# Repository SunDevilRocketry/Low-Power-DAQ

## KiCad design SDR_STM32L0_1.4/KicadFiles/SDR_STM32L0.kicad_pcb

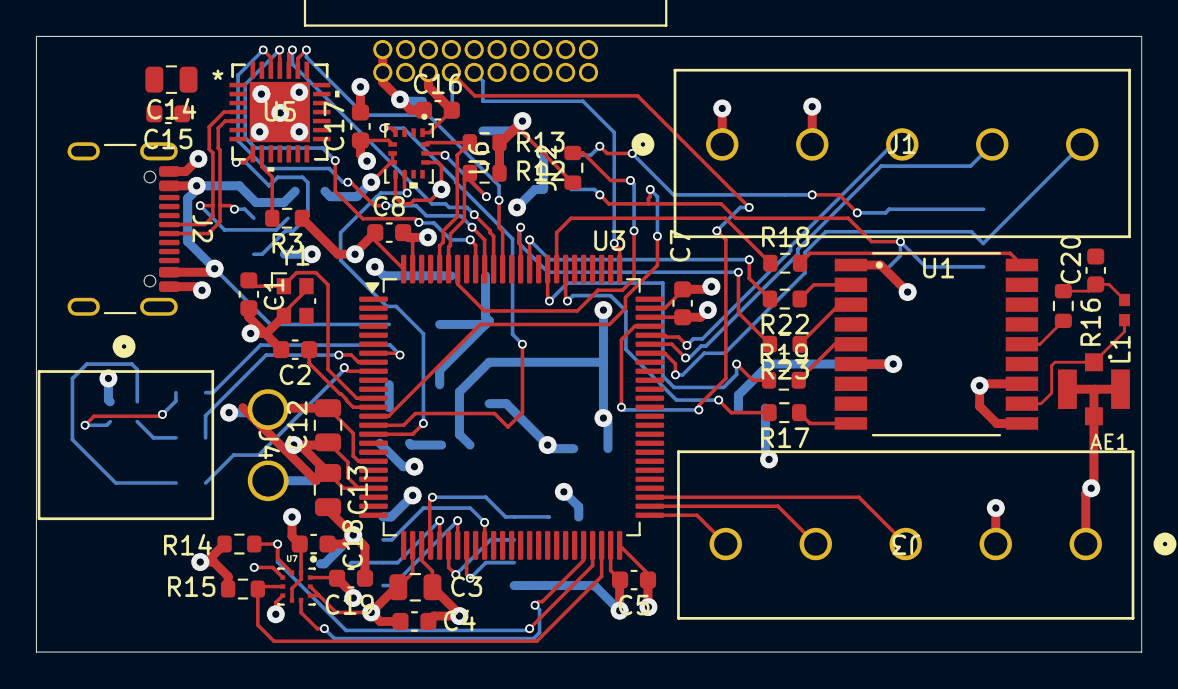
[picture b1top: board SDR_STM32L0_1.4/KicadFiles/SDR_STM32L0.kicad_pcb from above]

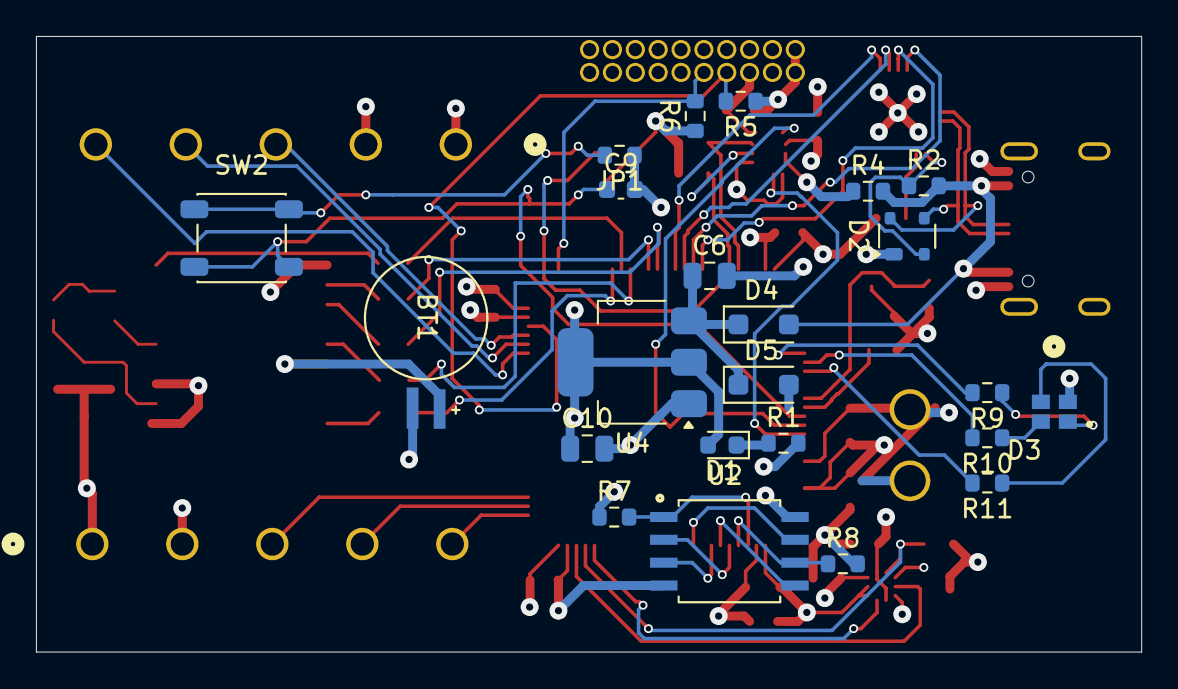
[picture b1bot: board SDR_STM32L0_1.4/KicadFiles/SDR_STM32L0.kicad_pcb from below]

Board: 4 copper layers, 61.4 x 34.2 mm, 68 parts (23 on the bottom side), 60 nets.

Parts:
AE1: 0734120110; 73412-0110
BT1: MS614SE-FL28E; MS621FE-FL11E
C1, C2: 25pF; C_0603_1608Metric
C3, C6: 10u; C_0805_2012Metric
C4, C5, C7, C8: 100n; C_0603_1608Metric
C9, C16, C17, C18, C19: 0.1uF; C_0603_1608Metric
C10: 22u; C_0805_2012Metric
C12: 1u; C_0805_2012Metric
C13: 0.1u; C_0805_2012Metric
C14: 4.7 uF; C_0805_2012Metric
C15: 0.1 uF; C_0603_1608Metric
C20: 0.01uF; C_0603_1608Metric
D1: LED; LED_0603_1608Metric
D2: SP0503BAHT; SOT-143
D3: LED_RGBA; CLMVC-FKA-CL1D1L71BB7C3C3
D4, D5: 5V; D_SOD-123F
H1, H2, H3, H4: MountingHole; MountingHole_2.2mm_M2
J1, J3: Conn_01x05_Pin; CONN_1935190_PXC
J2: USB_C_Receptacle_USB2.0_16P; USB_C_Receptacle_GCT_USB4105-xx-A_16P_TopMnt_Horizontal
J4: Conn_01x02_Pin; CONN2_647676-2_TEC
JP1, JP2: Open Jumper; R_0603_1608Metric
L1: 27nH; L-07C27NJV6T
P1: 3220-20-0200-00
R1: 1.5kR; R_0603_1608Metric
R2: 22.1 kOhm; R_0603_1608Metric
R3: 1kOhm; R_0603_1608Metric
R4: 47.5 kOhm; R_0603_1608Metric
R5, R6, R7, R8: 10k; R_0603_1608Metric
R9: 280; R_0603_1608Metric
R10: 82; R_0603_1608Metric
R11: 68; R_0603_1608Metric
R12, R13: 10kOhm; R_0603_1608Metric
R14, R15: 4.7k; R_0603_1608Metric
R16: 10; R_0603_1608Metric
R17, R18, R19, R22, R23: 33; R_0603_1608Metric
SW2: RESET SWITCH; SW_SPST_PTS647_Sx38
U1: MAX-8C-0-10; MAX-8C-0
U2: Engine-Controller_SST25VF040B-50-4I-S2AE-T; SST25VF040B-50-4I-S2AE-T
U3: STM32L083VBTx; LQFP-100_14x14mm_P0.5mm
U4: AMS1117-3.3; SOT-223-3_TabPin2
U5: CP2102N-Axx-xQFN28; QFN28_5X5_SIL
U6: BMI323
U7: BMP390
Y1: 25 MHz; Crystal_SMD_Abracon_ABM10-4Pin_2.5x2.0mm

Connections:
+3.3V: C3.1, C4.1, C5.1, C7.1, C8.1, C10.1, C12.1, C13.1, C14.1, C15.1, C16.1, C17.1, C18.1, C19.1, D1.2 (A), D3.4 (A), J1.2, J3.2, JP2.1 (A), P1.1, P1.2, R3.1, R5.1, R6.1, R7.1, R12.1, R13.1, R14.1, R15.1, U1.7 (VCC_IO), U1.8 (VCC), U2.8 (VDD), U3.22 (VDDA), U3.28 (VDD), U3.50 (VDD), U3.73 (VDD), U3.100 (VDD), U4.2 (VO), U5.6 (VDD), U5.7 (VREGIN), U6.5 (VDDIO), U6.8 (VDD), U6.12 (CSB), U7.1 (VDDIO), U7.6 (CSB), U7.10 (VDD)
/Movement/3V_BAK: BT1.1 (+), U1.6 (V_BCKP)
/Movement/GPS: AE1.1 (A), L1.2, U1.11 (RF_IN)
BOOT0: JP2.2 (B), U3.94 (BOOT0)
BOUTPUT: R11.2, U3.9 (PC15)
EXTI_10: U3.15 (PC0), U6.4 (INT1)
EXTI_11: U3.16 (PC1), U6.9 (INT2)
EXTI_13: R19.1, U3.84 (PD3)
EXTI_15: U3.46 (PE15), U7.7 (INT)
GND: AE1.2 (Shield), BT1.2 (-), C1.2, C2.2, C3.2, C4.2, C5.2, C6.2, C7.2, C8.2, C9.2, C10.2, C12.2, C13.2, C14.2, C15.2, C16.2, C17.2, C18.2, C19.2, C20.2, D2.1 (A), J1.1, J2.A1 (GND), J2.A12 (GND), J2.B1 (GND), J2.B12 (GND), J3.1, J4.1, JP1.1 (A), P1.3, P1.4, P1.5, P1.6, P1.8, P1.10, P1.12, P1.14, P1.16, P1.18, P1.20, R1.2, R4.1, R8.2, U1.1 (GND), U1.10 (GND), U1.12 (GND), U2.4 (VSS), U3.19 (VSSA), U3.27 (VSS), U3.49 (VSS), U3.74 (VSS), U3.99 (VSS), U4.1 (GND), U5.3 (GND), U5.29 (GND), U6.1 (SDO), U6.6 (GNDIO), U6.7 (GND), U7.3 (VSS), U7.5 (SDO), U7.8 (VSS), U7.9 (VSS), Y1.2, Y1.4
GOUTPUT: R10.2, U3.8 (PC14)
GPIO3_ADC: J3.5, U3.51 (PB12)
GPIO3_INPUT: J3.3, U3.53 (PB14)
GPIO3_OUTPUT: J3.4, U3.52 (PB13)
GPIO4_ADC: J1.5, U3.69 (PA10)
GPIO4_INPUT: J1.3, U3.71 (PA12)
GPIO4_OUTPUT: J1.4, U3.70 (PA11)
GPIO_GPSRST: R17.2, U3.82 (PD1)
GPIO_GPSSB: R18.1, U3.83 (PD2)
GPIO_OUTFL: U2.3 (*WP), U3.33 (PC4)
I2C1_SCL: R12.2, U3.95 (PB8), U6.13 (SCX)
I2C1_SDA: R13.2, U3.96 (PB9), U6.14 (SDX)
I2C2_SCL: R14.2, U3.47 (PB10), U7.2 (SCK)
I2C2_SDA: R15.2, U3.48 (PB11), U7.4 (SDI)
NRST: C9.1, P1.15, SW2.2 (B), U3.14 (NRST)
unnamed: C20.1, L1.1, R16.1
unnamed: D1.1 (K), R1.1
unnamed: D3.3 (BK), R11.1
unnamed: D3.2 (GK), R10.1
unnamed: D3.1 (RK), R9.1
unnamed: C6.1, D4.1 (K), D5.1 (K), U4.3 (VI)
unnamed: D5.2 (A), J4.2
unnamed: JP1.2 (B), SW2.1 (A)
unnamed: R19.2, U1.5 (EXTINT)
unnamed: R23.1, U1.3 (RXD)
unnamed: R22.1, U1.2 (TXD)
unnamed: R16.2, U1.14 (VCC_RF)
unnamed: R17.1, U1.9 (~RESET)
unnamed: R18.2, U1.18 (~SAFEBOOT)
unnamed: D2.4 (K), J2.A6 (D+), U5.4 (D+)
unnamed: D2.3 (K), J2.A7 (D-), U5.5 (D-)
unnamed: D2.2 (K), R2.1, U5.8 (VBUS)
unnamed: R3.2, U5.9 (~RST)
OSC_IN: C1.1, U3.12 (PH0), Y1.1
OSC_OUT: C2.1, U3.13 (PH1), Y1.3
ROUTPUT: R9.2, U3.7 (PC13)
SPI1_MISO: U2.2 (SO), U3.31 (PA6)
SPI1_MOSI: U2.5 (SI), U3.32 (PA7)
SPI1_NSS: R7.2, U2.1 (*CE), U3.29 (PA4)
SPI1_SCK: R8.1, U2.6 (SCK), U3.30 (PA5)
SYS_SWCLK: P1.9, R6.2, U3.76 (PA14)
SYS_SWDIO: P1.7, R5.2, U3.72 (PA13)
TIM3_CH3: U2.7 (*HOLD), U3.35 (PB0)
USART1_CTS: U3.90 (PB4), U5.24 (~RTS)
USART1_RTS: U3.89 (PB3), U5.23 (~CTS)
USART1_RX: U3.92 (PB6), U5.25 (RXD)
USART1_TX: U3.91 (PB5), U5.26 (TXD)
USART2_RX: R23.2, U3.87 (PD6)
USART2_TX: R22.2, U3.86 (PD5)
VBUS: D4.2 (A), J2.A4 (VBUS), J2.A9 (VBUS), J2.B4 (VBUS), J2.B9 (VBUS), R2.2, R4.2

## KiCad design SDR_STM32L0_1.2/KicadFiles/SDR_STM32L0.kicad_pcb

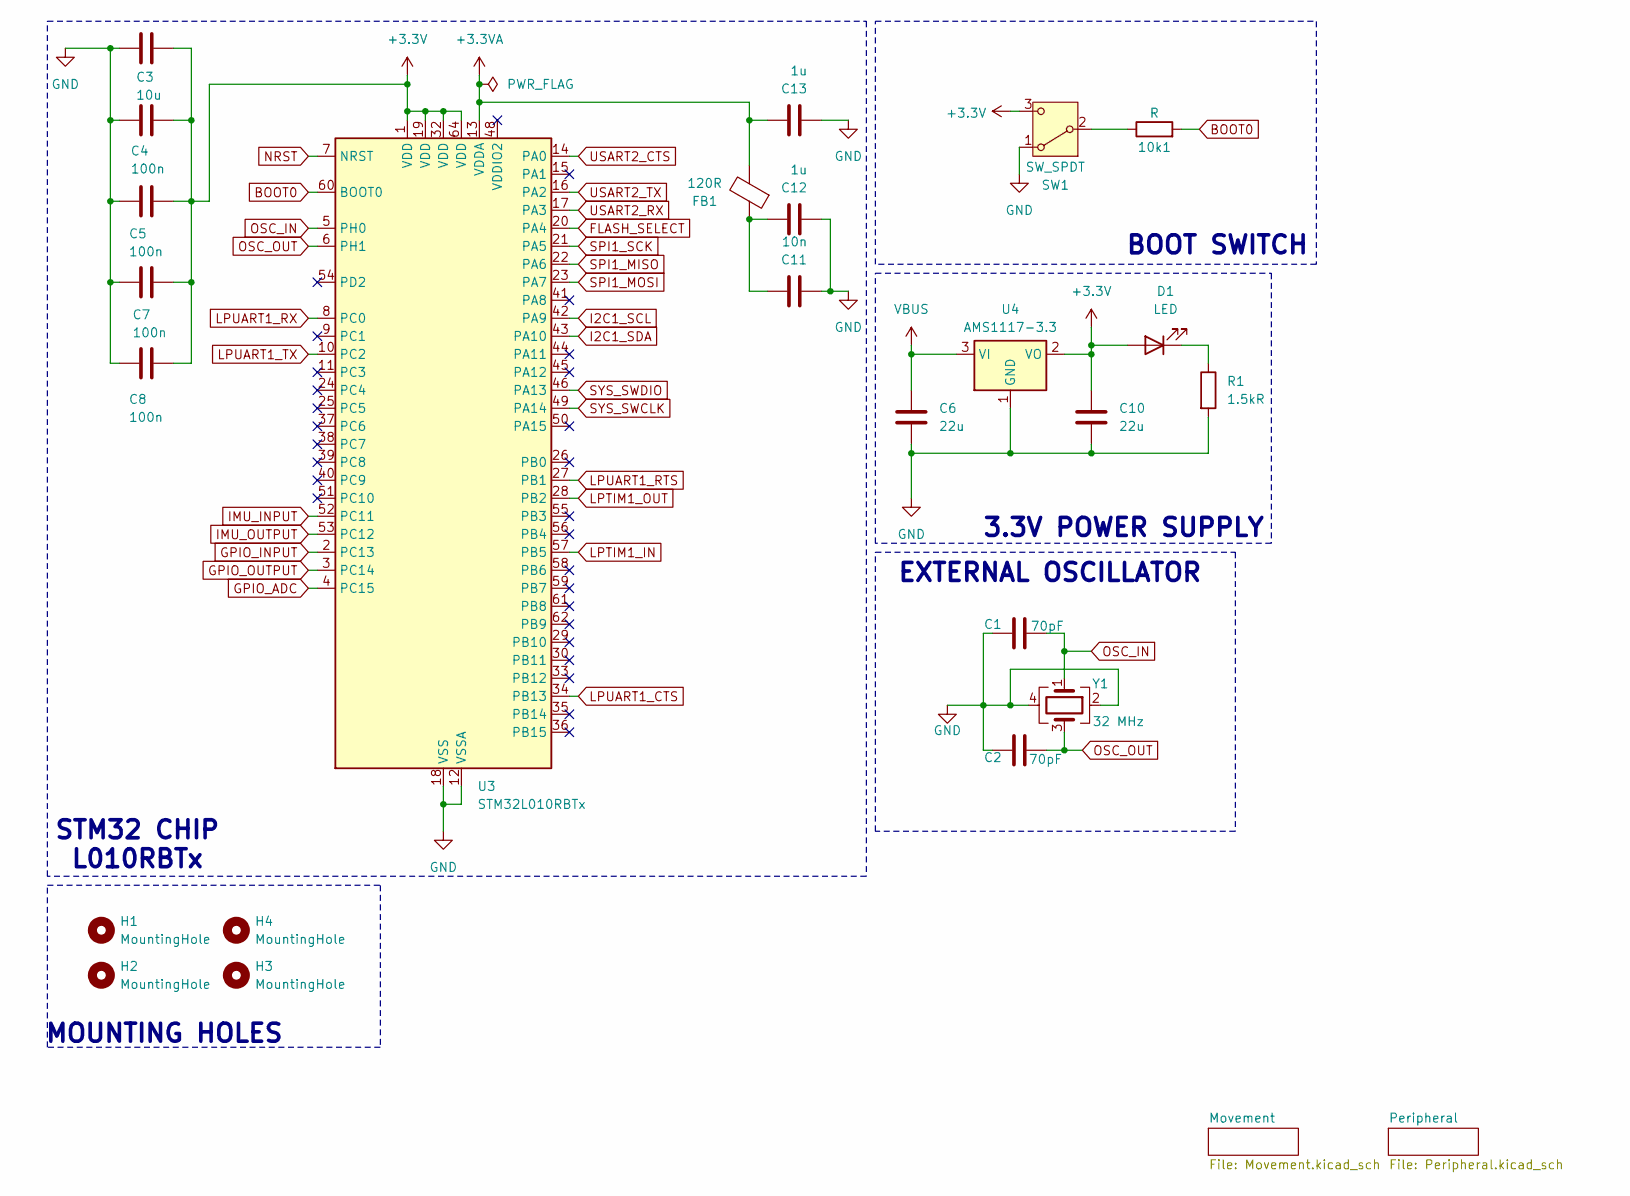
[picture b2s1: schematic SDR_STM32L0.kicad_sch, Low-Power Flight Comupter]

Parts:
10k1: R; R_0402_1005Metric
C1, C2: 70pF; C_0402_1005Metric
C3: 10u; C_0805_2012Metric
C4, C5, C7, C8: 100n; C_0402_1005Metric
C6, C10: 22u; C_0805_2012Metric
C11: 10n; C_0402_1005Metric
C12, C13: 1u; C_0805_2012Metric
D1: LED; LED_0603_1608Metric
FB1: 120R; L_0603_1608Metric
H1, H2, H3, H4: MountingHole; MountingHole_2.2mm_M2
R1: 1.5kR; R_0402_1005Metric
SW1: SW_SPDT; SW_SPST_B3U-1100P-B
U3: STM32L010RBTx; LQFP-64_10x10mm_P0.5mm
U4: AMS1117-3.3; SOT-223-3_TabPin2
Y1: 32 MHz; Crystal_SMD_Abracon_ABM10-4Pin_2.5x2.0mm

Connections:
+3.3V: C3.1, C4.1, C5.1, C7.1, C8.1, C10.1, D1.2 (A), SW1.3 (C), U3.1 (VDD), U3.19 (VDD), U3.32 (VDD), U3.64 (VDD), U4.2 (VO); also elsewhere on the board
+3.3VA: C13.1, FB1.2, U3.13 (VDDA)
BOOT0: 10k1.2, U3.60 (BOOT0)
FLASH_SELECT: U3.20 (PA4); also elsewhere on the board
GND: C1.2, C2.2, C3.2, C4.2, C5.2, C6.2, C7.2, C8.2, C10.2, C11.2, C12.2, C13.2, R1.2, SW1.1 (A), U3.12 (VSSA), U3.18 (VSS), U3.31 (VSS), U3.47 (VSS), U3.63 (VSS), U4.1 (GND), Y1.2, Y1.4; also elsewhere on the board
GPIO_ADC: U3.4 (PC15); also elsewhere on the board
GPIO_INPUT: U3.2 (PC13); also elsewhere on the board
GPIO_OUTPUT: U3.3 (PC14); also elsewhere on the board
I2C1_SCL: U3.42 (PA9); also elsewhere on the board
I2C1_SDA: U3.43 (PA10); also elsewhere on the board
IMU_INPUT: U3.52 (PC11); also elsewhere on the board
IMU_OUTPUT: U3.53 (PC12); also elsewhere on the board
LPTIM1_IN: U3.57 (PB5); also elsewhere on the board
LPTIM1_OUT: U3.28 (PB2); also elsewhere on the board
LPUART1_CTS: U3.34 (PB13); also elsewhere on the board
LPUART1_RTS: U3.27 (PB1); also elsewhere on the board
LPUART1_RX: U3.8 (PC0); also elsewhere on the board
LPUART1_TX: U3.10 (PC2); also elsewhere on the board
NRST: U3.7 (NRST); also elsewhere on the board
unnamed: C11.1, C12.1, FB1.1
unnamed: D1.1 (K), R1.1
unnamed: 10k1.1, SW1.2 (B)
OSC_IN: C1.1, U3.5 (PH0), Y1.1
OSC_OUT: C2.1, U3.6 (PH1), Y1.3
SPI1_MISO: U3.22 (PA6); also elsewhere on the board
SPI1_MOSI: U3.23 (PA7); also elsewhere on the board
SPI1_SCK: U3.21 (PA5); also elsewhere on the board
SYS_SWCLK: U3.49 (PA14); also elsewhere on the board
SYS_SWDIO: U3.46 (PA13); also elsewhere on the board
USART2_CTS: U3.14 (PA0); also elsewhere on the board
USART2_RX: U3.17 (PA3); also elsewhere on the board
USART2_TX: U3.16 (PA2); also elsewhere on the board
VBUS: C6.1, U4.3 (VI); also elsewhere on the board

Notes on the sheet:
MOUNTING HOLES
STM32 CHIP L010RBTx
EXTERNAL OSCILLATOR
3.3V POWER SUPPLY
BOOT SWITCH

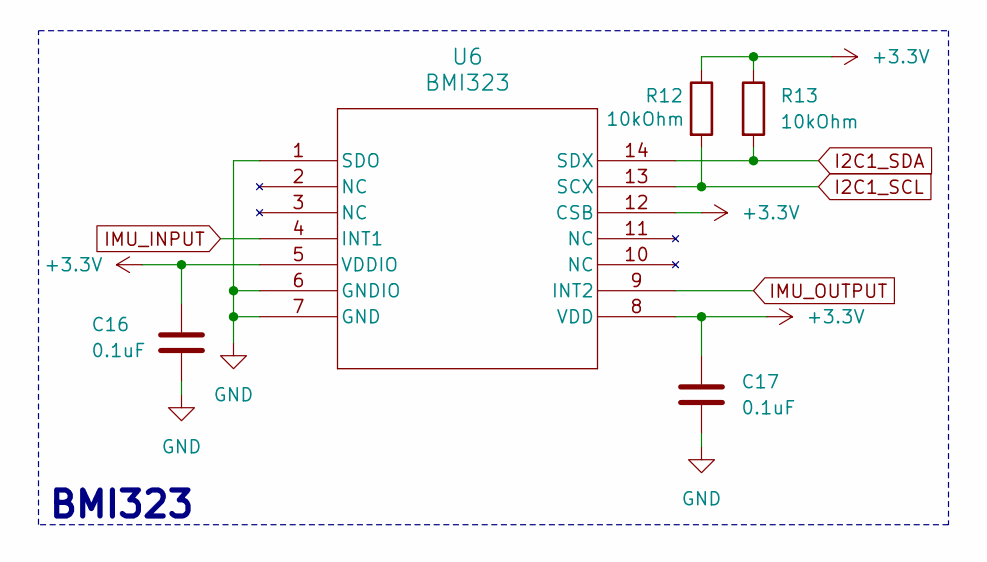
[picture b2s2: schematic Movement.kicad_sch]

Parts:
C16, C17: 0.1uF; C_0402_1005Metric
R12, R13: 10kOhm; R_0402_1005Metric
U6: BMI323

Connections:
+3.3V: C16.1, C17.1, R12.1, R13.1, U6.5 (VDDIO), U6.8 (VDD), U6.12 (CSB); also elsewhere on the board
GND: C16.2, C17.2, U6.1 (SDO), U6.6 (GNDIO), U6.7 (GND); also elsewhere on the board
I2C1_SCL: R12.2, U6.13 (SCX); also elsewhere on the board
I2C1_SDA: R13.2, U6.14 (SDX); also elsewhere on the board
IMU_INPUT: U6.4 (INT1); also elsewhere on the board
IMU_OUTPUT: U6.9 (INT2); also elsewhere on the board

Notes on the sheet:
BMI323

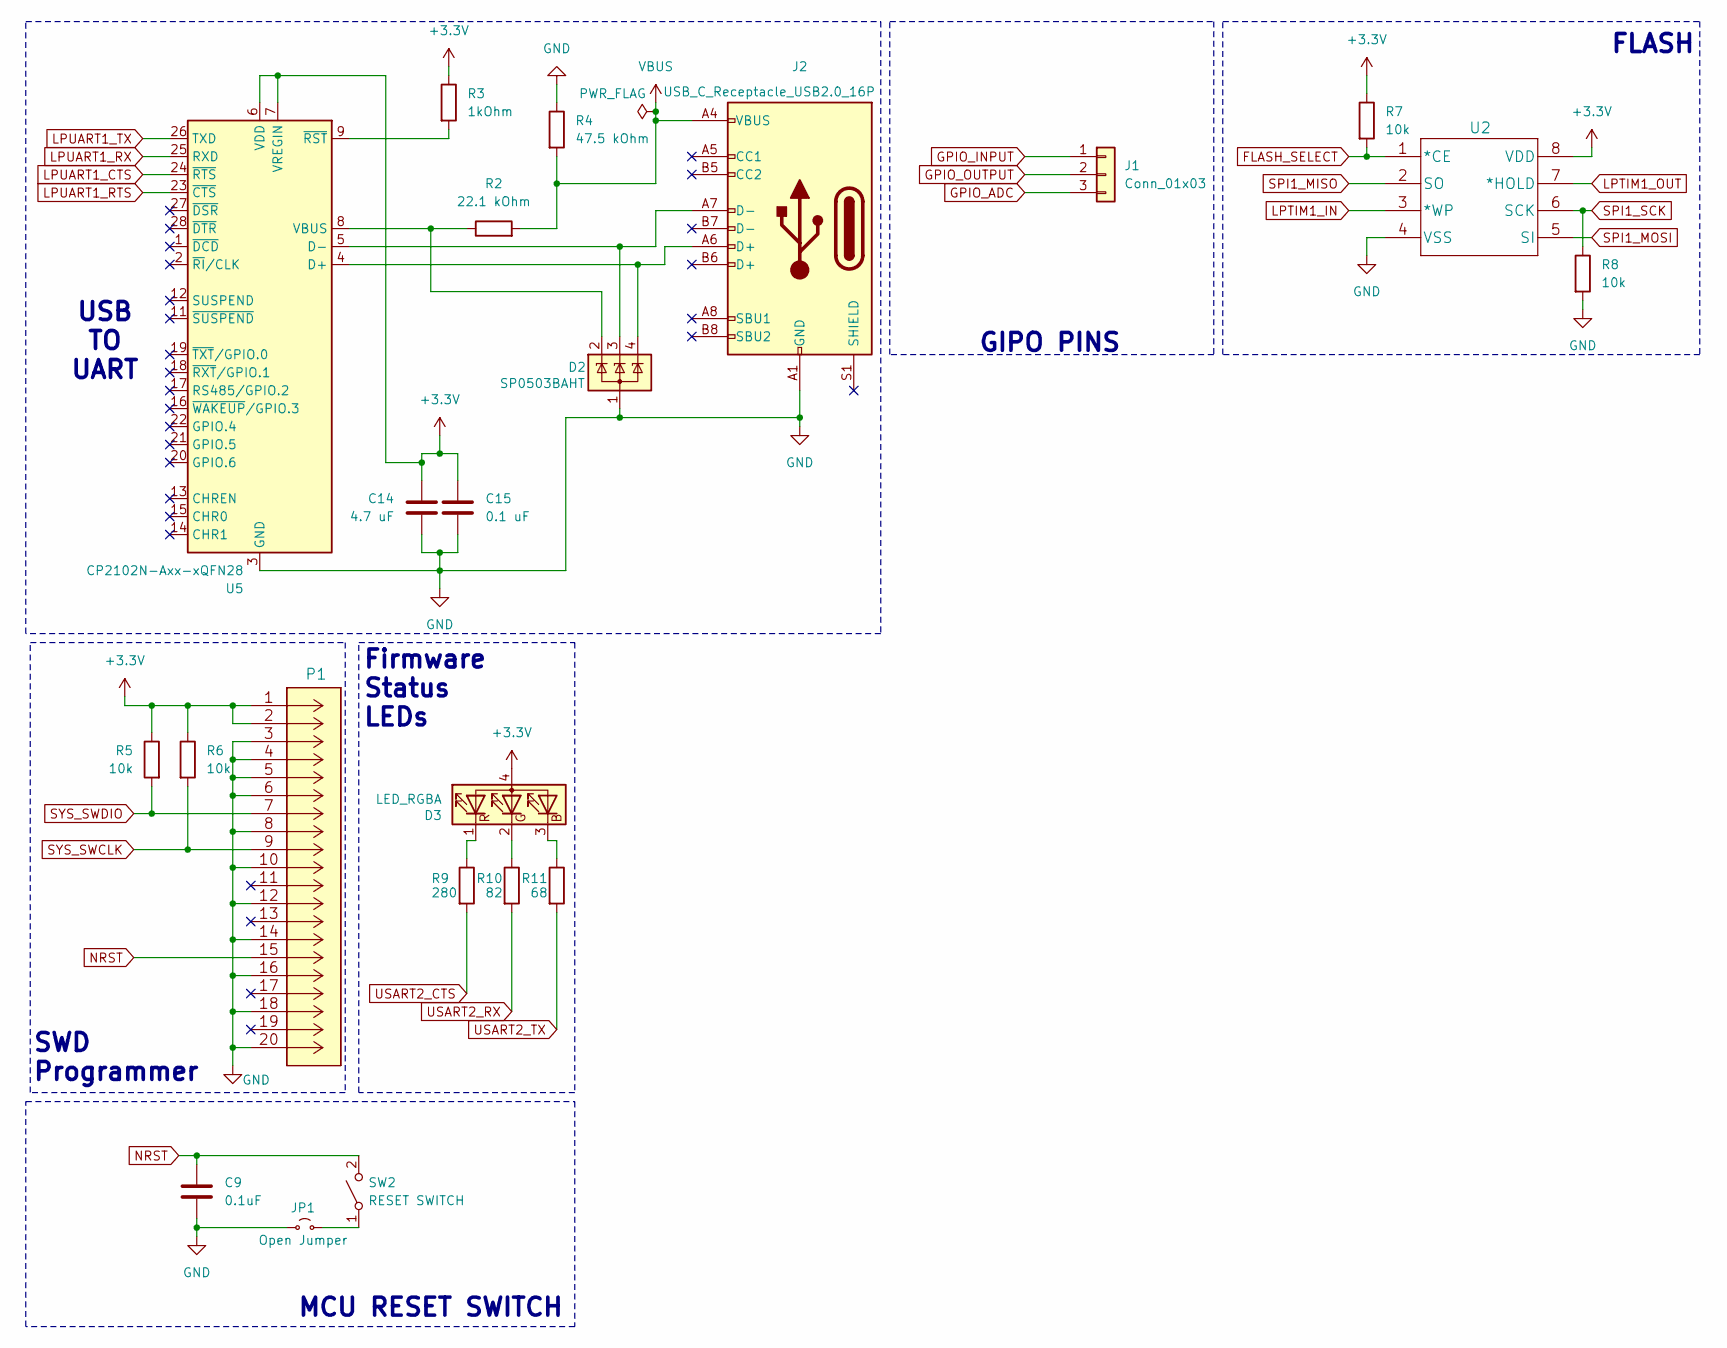
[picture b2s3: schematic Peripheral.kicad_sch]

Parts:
C9: 0.1uF; C_0402_1005Metric
C14: 4.7 uF; C_0805_2012Metric
C15: 0.1 uF; C_0402_1005Metric
D2: SP0503BAHT; SOT-143
D3: LED_RGBA; LED_Cree-PLCC4_5x5mm_CW
J1: Conn_01x03; JST_EH_S3B-EH_1x03_P2.50mm_Horizontal
J2: USB_C_Receptacle_USB2.0_16P; USB_C_Receptacle_GCT_USB4105-xx-A_16P_TopMnt_Horizontal
JP1: Open Jumper; TestPoint_2Pads_Pitch2.54mm_Drill0.8mm
P1: 3220-20-0200-00
R2: 22.1 kOhm; R_0603_1608Metric
R3: 1kOhm; R_0402_1005Metric
R4: 47.5 kOhm; R_0603_1608Metric
R5, R6, R7, R8: 10k; R_0402_1005Metric
R9: 280; R_0402_1005Metric
R10: 82; R_0402_1005Metric
R11: 68; R_0402_1005Metric
SW2: RESET SWITCH; SW_DIP_SPSTx01_Slide_9.78x4.72mm_W7.62mm_P2.54mm
U2: Engine-Controller_SST25VF040B-50-4I-S2AE-T; SST25VF040B-50-4I-S2AE-T
U5: CP2102N-Axx-xQFN28; QFN-28-1EP_5x5mm_P0.5mm_EP3.35x3.35mm

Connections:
+3.3V: C14.1, C15.1, D3.4 (A), P1.1, P1.2, R3.1, R5.1, R6.1, R7.1, U2.8 (VDD), U5.6 (VDD), U5.7 (VREGIN); also elsewhere on the board
FLASH_SELECT: R7.2, U2.1 (*CE); also elsewhere on the board
GND: C9.2, C14.2, C15.2, D2.1 (A), J2.A1 (GND), J2.A12 (GND), J2.B1 (GND), J2.B12 (GND), JP1.1 (A), P1.3, P1.4, P1.5, P1.6, P1.8, P1.10, P1.12, P1.14, P1.16, P1.18, P1.20, R4.1, R8.2, U2.4 (VSS), U5.3 (GND), U5.29 (GND); also elsewhere on the board
GPIO_ADC: J1.3; also elsewhere on the board
GPIO_INPUT: J1.1; also elsewhere on the board
GPIO_OUTPUT: J1.2; also elsewhere on the board
LPTIM1_IN: U2.3 (*WP); also elsewhere on the board
LPTIM1_OUT: U2.7 (*HOLD); also elsewhere on the board
LPUART1_CTS: U5.24 (~RTS); also elsewhere on the board
LPUART1_RTS: U5.23 (~CTS); also elsewhere on the board
LPUART1_RX: U5.25 (RXD); also elsewhere on the board
LPUART1_TX: U5.26 (TXD); also elsewhere on the board
NRST: C9.1, P1.15, SW2.2 (B); also elsewhere on the board
unnamed: D3.3 (BK), R11.1
unnamed: D3.2 (GK), R10.1
unnamed: D3.1 (RK), R9.1
unnamed: JP1.2 (B), SW2.1 (A)
unnamed: D2.4 (K), J2.A6 (D+), U5.4 (D+)
unnamed: D2.3 (K), J2.A7 (D-), U5.5 (D-)
unnamed: D2.2 (K), R2.1, U5.8 (VBUS)
unnamed: R3.2, U5.9 (~RST)
SPI1_MISO: U2.2 (SO); also elsewhere on the board
SPI1_MOSI: U2.5 (SI); also elsewhere on the board
SPI1_SCK: R8.1, U2.6 (SCK); also elsewhere on the board
SYS_SWCLK: P1.9, R6.2; also elsewhere on the board
SYS_SWDIO: P1.7, R5.2; also elsewhere on the board
USART2_CTS: R9.2; also elsewhere on the board
USART2_RX: R10.2; also elsewhere on the board
USART2_TX: R11.2; also elsewhere on the board
VBUS: J2.A4 (VBUS), J2.A9 (VBUS), J2.B4 (VBUS), J2.B9 (VBUS), R2.2, R4.2; also elsewhere on the board

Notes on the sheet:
SWD Programmer
Firmware Status LEDs
FLASH
MCU RESET SWITCH
USB TO UART
GIPO PINS

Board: 2 copper layers, 51 parts (0 on the bottom side), 41 nets, no tracks yet.

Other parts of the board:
SERIAL WIRE DEBUG: 3220-20-0200-00

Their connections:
+3.3V: SERIAL WIRE DEBUG.1, SERIAL WIRE DEBUG.2; also elsewhere on the board
GND: SERIAL WIRE DEBUG.3, SERIAL WIRE DEBUG.4, SERIAL WIRE DEBUG.5, SERIAL WIRE DEBUG.6, SERIAL WIRE DEBUG.8, SERIAL WIRE DEBUG.10, SERIAL WIRE DEBUG.12, SERIAL WIRE DEBUG.14, SERIAL WIRE DEBUG.16, SERIAL WIRE DEBUG.18, SERIAL WIRE DEBUG.20; also elsewhere on the board
NRST: SERIAL WIRE DEBUG.15; also elsewhere on the board
SYS_SWCLK: SERIAL WIRE DEBUG.9; also elsewhere on the board
SYS_SWDIO: SERIAL WIRE DEBUG.7; also elsewhere on the board

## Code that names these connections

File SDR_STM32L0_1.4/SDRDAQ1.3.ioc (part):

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Mcu.Name=STM32L083V(B-Z)Tx
Mcu.Package=LQFP100
Mcu.UserName=STM32L083VBTx
PA0.Mode=CTS_Only
PA0.Signal=USART2_CTS
PA10.Mode=Asynchronous
PA10.Signal=USART1_RX
PA12.Signal=GPIO_Output
PA13.Mode=Serial_Wire
PA13.Signal=SYS_SWDIO
PA14.Mode=Serial_Wire
PA14.Signal=SYS_SWCLK
PA2.Mode=Asynchronous
PA2.Signal=USART2_TX
PA3.Mode=Asynchronous
PA3.Signal=USART2_RX
PA5.Mode=Full_Duplex_Master
PA5.Signal=SPI1_SCK
PA6.Mode=CTS_RTS
PA6.Signal=LPUART1_CTS
PA7.Mode=Full_Duplex_Master
PA7.Signal=SPI1_MOSI
PA9.Mode=Asynchronous
PA9.Signal=USART1_TX
PB1.Mode=CTS_RTS
PB1.Signal=LPUART1_RTS
PB10.Mode=I2C
PB10.Signal=I2C2_SCL
PB11.Mode=I2C
PB11.Signal=I2C2_SDA
PB13.Signal=GPIO_Input
PB14.Signal=GPIO_Output
PB15.Signal=GPIO_Analog
PB2.Mode=WaveformGeneration
PB2.Signal=LPTIM1_OUT
PB6.Mode=I2C
PB6.Signal=I2C1_SCL
PB7.Mode=I2C
PB7.Signal=I2C1_SDA
PC0.Mode=Counts_external_clock_standalone_1X_occur1
PC0.Signal=LPTIM1_IN1
PC1.Mode=Asynchronous
PC1.Signal=LPUART1_TX
PC13.Signal=GPIO_Output
PC14-OSC32_IN.Signal=GPIO_Input
PC15-OSC32_OUT.Signal=GPIO_Analog
PC2.Signal=GPIO_Analog
PC3.Signal=GPIO_Output
PC5.Mode=Asynchronous
PC5.Signal=LPUART1_RX
PD0.Signal=GPIO_Input
PD1.Signal=GPIO_Output
PD10.Signal=GPIO_Output
PD11.Signal=GPIO_Output
PD12.Signal=GPIO_Output
PD2.Signal=GPIO_Analog
PD8.Signal=GPIO_Output
PD9.Signal=GPIO_Input
PE10.Signal=GPIO_Output
PE14.Mode=Full_Duplex_Master
PE14.Signal=SPI1_MISO
PE15.Signal=GPIO_Output
PH0-OSC_IN.Mode=HSE-External-Oscillator
PH0-OSC_IN.Signal=RCC_OSC_IN
PH1-OSC_OUT.Mode=HSE-External-Oscillator
PH1-OSC_OUT.Signal=RCC_OSC_OUT
PH10.Signal=GPIO_Input
RCC.HSE_VALUE=8000000
RCC.SYSCLKFreq_VALUE=2097000
board=custom

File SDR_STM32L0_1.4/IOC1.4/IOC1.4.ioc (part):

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Mcu.Name=STM32L083V(B-Z)Tx
Mcu.Package=LQFP100
Mcu.UserName=STM32L083VBTx
PA0.Signal=GPIO_Analog
PA1.Signal=GPIO_Output
PA10.Signal=GPIO_Analog
PA11.Signal=GPIO_Output
PA12.Signal=GPIO_Input
PA13.Mode=Serial_Wire
PA13.Signal=SYS_SWDIO
PA14.Mode=Serial_Wire
PA14.Signal=SYS_SWCLK
PA2.Signal=GPIO_Input
PA4.Mode=NSS_Signal_Hard_Output
PA4.Signal=SPI1_NSS
PA5.Mode=Full_Duplex_Master
PA5.Signal=SPI1_SCK
PA6.Mode=Full_Duplex_Master
PA6.Signal=SPI1_MISO
PA7.Mode=Full_Duplex_Master
PA7.Signal=SPI1_MOSI
PB0.Signal=S_TIM3_CH3
PB10.Mode=I2C
PB10.Signal=I2C2_SCL
PB11.Mode=I2C
PB11.Signal=I2C2_SDA
PB12.Signal=GPIO_Analog
PB13.Signal=GPIO_Output
PB14.Signal=GPIO_Input
PB3.Mode=CTS_RTS
PB3.Signal=USART1_RTS
PB4.Mode=CTS_RTS
PB4.Signal=USART1_CTS
PB6.Mode=Asynchronous
PB6.Signal=USART1_TX
PB7.Mode=Asynchronous
PB7.Signal=USART1_RX
PB8.Mode=I2C
PB8.Signal=I2C1_SCL
PB9.Mode=I2C
PB9.Signal=I2C1_SDA
PC13.Signal=GPIO_Output
PC14-OSC32_IN.Signal=GPIO_Output
PC15-OSC32_OUT.Signal=GPIO_Output
PC4.Signal=GPIO_Output
PD1.Signal=GPIO_Output
PD2.Signal=GPIO_Output
PD3.Signal=GPXTI3
PD4.Signal=GPXTI4
PD5.Mode=Asynchronous
PD5.Signal=USART2_TX
PD6.Mode=Asynchronous
PD6.Signal=USART2_RX
PE0.Signal=GPXTI0
PE1.Signal=GPXTI1
PE15.Signal=GPXTI15
PE2.Signal=GPIO_Input
PE3.Signal=GPIO_Output
PE4.Signal=GPIO_Analog
RCC.HSE_VALUE=8000000
RCC.SYSCLKFreq_VALUE=2097000
board=custom

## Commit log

2024-09-27 Prettified files + updated pinout file
2024-10-25 PCB Design 1.2
    Added footprints, 3d models, and basic layout
2024-11-01 added 1.2 back
2024-11-15 work
2024-11-15 begin routing
2024-11-21 Finished PCB Routing
2025-04-16 Upgrade
    Changed a few peripherals (less ports, +/- on ports, switched jumpers, switched pinouts), and made new shematic
